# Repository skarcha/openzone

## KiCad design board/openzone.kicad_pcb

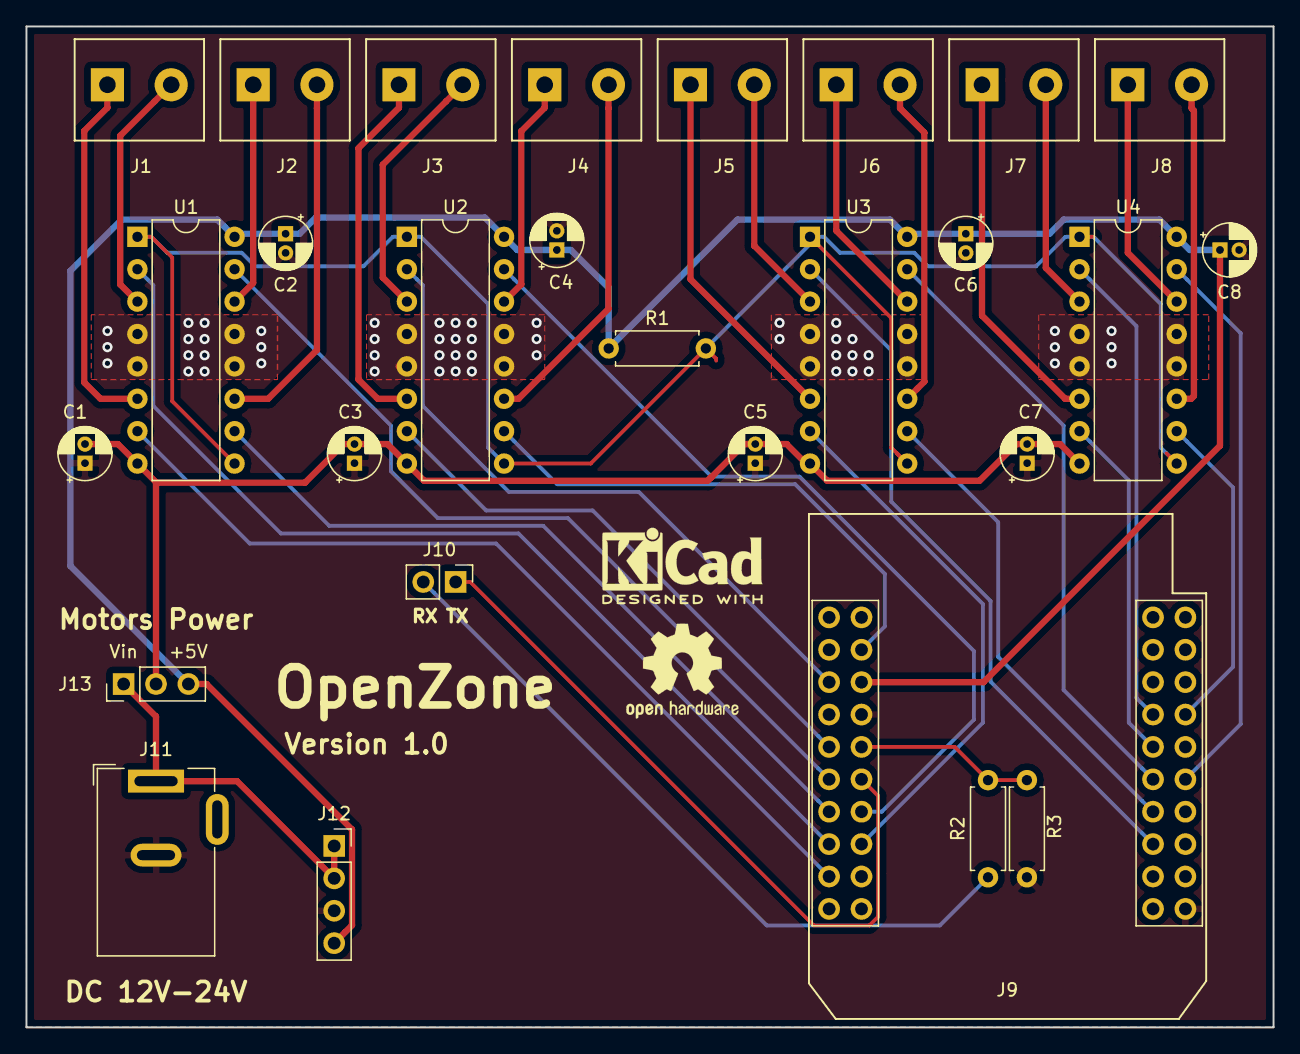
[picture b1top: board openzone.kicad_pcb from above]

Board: 2 copper layers, 97.8 x 78.5 mm, 28 parts (0 on the bottom side), 40 nets.

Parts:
C1, C3, C5, C7: 1uF; CP_Radial_D4.0mm_P1.50mm
C2, C4, C6, C8: 0.1uF; CP_Radial_D4.0mm_P1.50mm
J1: Motor1; KF301-2P-5
J2: Motor2; KF301-2P-5
J3: Motor3; KF301-2P-5
J4: Motor4; KF301-2P-5
J5: Motor5; KF301-2P-5
J6: Motor6; KF301-2P-5
J7: Motor7; KF301-2P-5
J8: Motor8; KF301-2P-5
J9: WEMOS_D1_MINI_ESP32; WEMOS_D1_MINI32_UP
J10: AC serial; PinHeader_1x02_P2.54mm_Vertical
J11: Power Supply; BarrelJack_Wuerth_6941xx301002
J12: Step Down Power Supply; PinSocket_1x04_P2.54mm_Vertical
J13: Motor Power Supply Selector; PinHeader_1x03_P2.54mm_Vertical
R1, R3: 10K; R_Axial_DIN0207_L6.3mm_D2.5mm_P7.62mm_Horizontal
R2: 4,7K; R_Axial_DIN0207_L6.3mm_D2.5mm_P7.62mm_Horizontal
U1, U2, U3, U4: SN754410; DIP-16_W7.62mm

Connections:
+5V: C2.1, C4.1, C6.1, C8.1, J9.13, J12.4, J13.3, R1.1, U1.16, U2.16, U3.16, U4.16
+12V: J11.1, J12.1, J12.2, J13.1
DEnable: R1.2, U1.1, U1.9, U2.1, U2.9, U3.1, U3.9, U4.1, U4.9
GND: C1.1, C2.2, C3.1, C4.2, C5.1, C6.2, C7.1, C8.2, J9.1, J9.14, J9.40, J11.2, J12.3, R3.1, U1.4, U1.5, U1.12, U1.13, U2.4, U2.5, U2.12, U2.13, U3.4, U3.5, U3.12, U3.13, U4.4, U4.5, U4.12, U4.13
IO02: J9.8, U2.2
IO04: J9.6, U2.7
IO05: J9.27, U4.2
IO12: J9.5, U1.15
IO14: J9.34, U4.10
IO15: J9.12, U2.10
IO16_RX: J9.15, R2.2, R3.2
IO17_TX: J9.16, J10.1
IO18: J9.24, U3.10
IO19: J9.25, U3.15
IO21: J9.17, U2.15
IO22: J9.18, U3.7
IO23: J9.26, U4.7
IO25: J9.3, U1.2
IO26: J9.23, U3.2
IO27: J9.2, U1.7
IO32: J9.4, U1.10
IO33: J9.36, U4.15
MotorPWR: C1.2, C3.2, C5.2, C7.2, J13.2, U1.8, U2.8, U3.8, U4.8
unnamed: J1.1, U1.6
unnamed: J1.2, U1.3
unnamed: J2.1, U1.14
unnamed: J2.2, U1.11
unnamed: J3.1, U2.6
unnamed: J3.2, U2.3
unnamed: J4.1, U2.14
unnamed: J4.2, U2.11
unnamed: J5.1, U3.6
unnamed: J5.2, U3.3
unnamed: J6.1, U3.14
unnamed: J6.2, U3.11
unnamed: J7.1, U4.6
unnamed: J7.2, U4.3
unnamed: J8.1, U4.14
unnamed: J8.2, U4.11
unnamed: J10.2, R2.1

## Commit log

2018-10-11 A lot of changes
    Including:
    * ESP32 relocation to improve WiFi signal strength.
    * Voltage divider for serial TTL communication with Air Conditioner.
    * New PCB terminals footprint. My own.
    * Adds OpenZone logo.
2018-10-13 Updates plot config
    Adds output directory for Gerber files and other plot options.
2018-11-08 Deletes unused segment
